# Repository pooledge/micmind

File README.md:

# Micmind - remotely controlled microphone stand prototype (Air P3)
Arduino based microphone stand controlled remotely within a Max/MSP built standalone application. Micmind Air uses a pair of XBee Pro 868 operating in API mode for wireless communication.

This repository includes:
* Arduino sketch to upload on a Pro Mini 328 (5V)
* MaxMSP patch to build a standalone host application for Mac or Windows
* EAGLE files containing schematic and board layouts
* OpenSCAD file enclosure model to build and export in STL format for futher 3D printing
* Xbee firmware XML files used by XCTU
* XML file containing some commands for developing and debuging purposes in XCTU
* Icon file and its .psd source used for the Macintosh standalone

Software versions used at the time building the prototype:
* Mac OS X 10.9.5
* Arduino 1.0.6
* MaxMSP 5.1.3
* EAGLE 7.2.0
* OpenSCAD 2015.03-1
* XCTU 6.2.0
* Photoshop CS6

## What is it about?

Micmind is simply a microphone stand for seamless indoor stereo recording, controlled remotely. So called AB-stereo technique, commonly used in classical music recording utilizes a pair of omnidirectional microphones. While collecting both time-of-arrival and level difference information and being very efficient, this method demands considerations and decisions often being made on-the-fly, also involving some sort of luck. While familiar with theory, sound engineer may still play quite a long time with a stand position and the distance between two microphones as those factors have dramatic impact on the sound image. Very often classical recordings are made with AB only and within low-time conditions, especially those low paid sound engineer jobs if you know what I mean. Now, to tell a long story short, being able to adjust AB parameters from some distance brings following advantages:
* The need to cover multiple meters between control and recording rooms is eliminated (meh)
* Key adjustments applied on-the-fly with their effect to be observed instantly, thus not only the result is achieved in a more efficient way but also the learn effect of using this recording technique increases dramatically.

Micmind is not pretending to be unique, as of 2016 there are different similar products currently available: Remote-Mast, Robo-Mic, Stereoblade, Optogate... etc. However each of them has their disadvantages: summed up they are either too bulky, expensive, loud or not suitable for AB recording due to its size or construction principles.

## Key features
* Up to 1.2km line-of-sight controlling distance
* No frames, rails or cables - end position is freely adjustable
* Linear and rotation movement modes
* Stereo base distance adjustment from 1cm to 99cm
* Impact noise isolation
* Virtual capacitor technology for smoother motion
* Simple and robust modular construction
* Stable grip and low-noise operation

## Safety
* Permanent motor braking while stall
* Panic mode if connection to host computer is lost or not available
* Clear visual status indication both host- and client-side

## Power management
* Single 6c lithium-polymer battery for hours of operation, 5Ah, built-in
* Seamless charging with no disassembly
* Operation/charging mode selector switch

## Chassis
* Main stand built upon freely available Manfrotto 1005BAC tripod and 100mm mecanum wheels
* Simple and efficient 24VDC motors

## Future demands
* ~~Future of Micmind is the future of wireless microphoning. Though our wired initial prototype already serves at it's best, imagine a microphone stand, that can move freely, with no cables, with no boundaries.~~
* ~~Along the embedding of an Xbee modules both host- and client-side for seamless and stable communication, a non-wired future release of Micmind also demands some wireless components to transmit audio signals from floating microphones.~~
* Though a mechanism for height adjustment was initially planned, it was dropped later, as it wasn't possible to retrieve such a non-bulky, low-load, high-stroke component as a serial produced unit. A custom build of a telescopic pipe however may solve this problem, bringing to life an amazing possibility to adjust microphones' position in absolutely all extents without dramatically reducing stand's mobility and stability. 
* Since a homo drive proved to be the right choice for a moveable mic stand, even slightly bigger wheels will instantly allow more stability and better weight distribution - for preciser handling when overcoming boundaries such as cables, height differences of various surfaces and their defects.
* Quieter motors is just a matter of costs, since all their characteristics are already known and have been proved as appropriate. Using gearless motors instead of geared ones might be a good decision, the more so, because the programmable hardware layer of Micmind easily allows their embedding. In that way it is definitely possible to achieve a smoother operation with significant lower noise emission - an important factor for recording classical music known for its wide dynamic range and low SNR.
* ~~PCB, a printed circuit board. This text's author spent two weeks soldering a circuit board for the prototype. Involving more components in the future simply won't leave any choice on this one. For the efficiency of work!~~
* Undo/redo functionality for fast A/B testing

## Disclaimer
This project is being realized as a part of the master degree diploma at the sound engineering faculty of University of music and performing arts in Vienna, Austria.
This disclaimer is being updated constantly along required regulations.

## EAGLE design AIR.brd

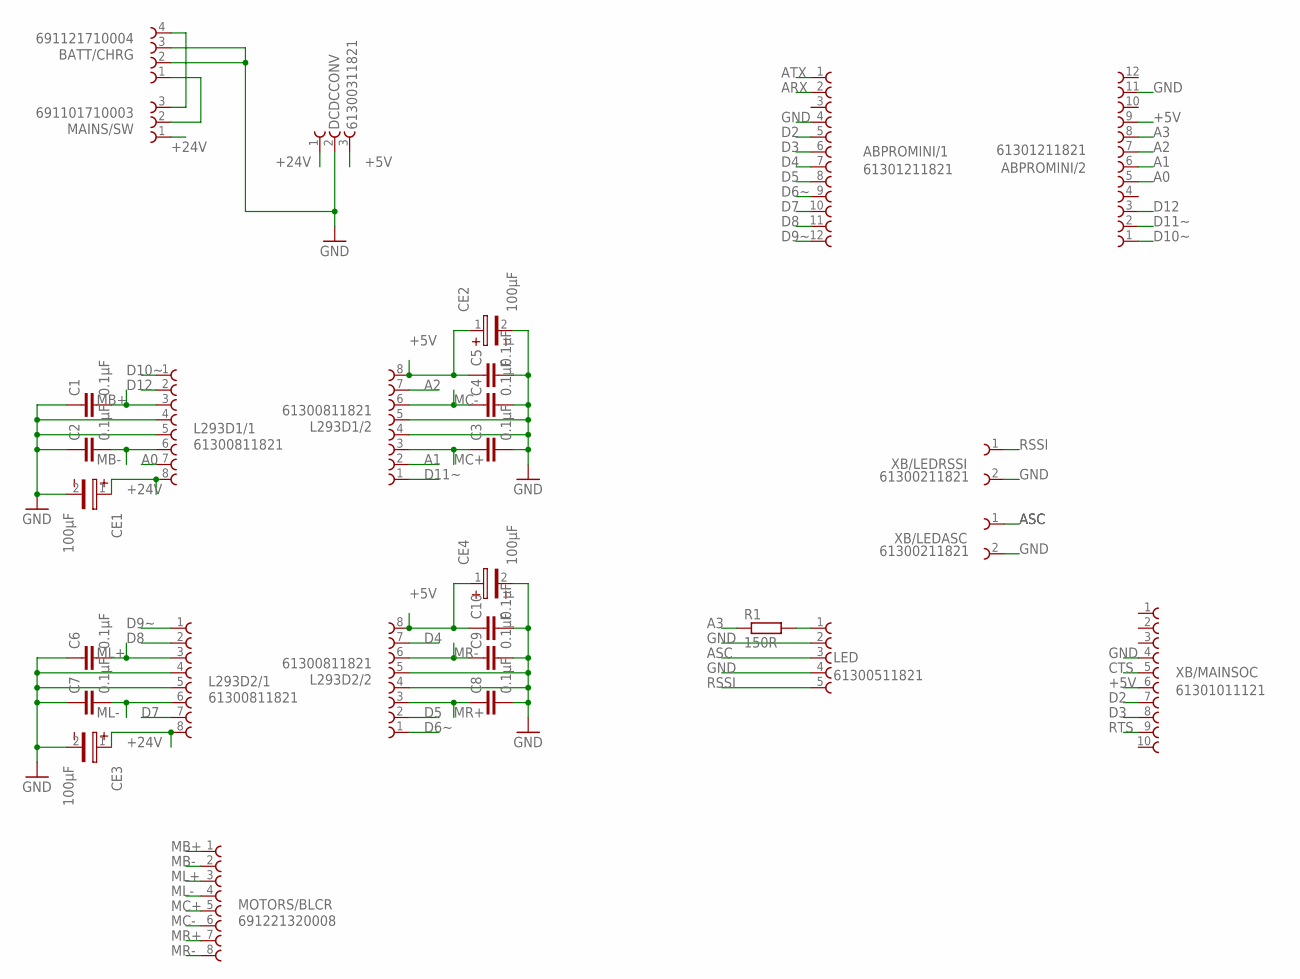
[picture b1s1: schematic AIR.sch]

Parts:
ABPROMINI/1, ABPROMINI/2: 61301211821
BATT/CHRG: 691121710004
C1, C2, C3, C4, C5, C6, C7, C8, C9, C10: 0.1µF; C025-025X050
CE1, CE2, CE3, CE4: 100µF; 8X3.5X0.9(DXAXB)
DCDCCONV: 61300311821
L293D1/1, L293D1/2, L293D2/1, L293D2/2: 61300811821
LED: 61300511821
MAINS/SW: 691101710003
MOTORS/BLCR: 691221320008
R1: 150R; 0204/7
XB/LEDASC: 61300211821
XB/LEDRSSI: 61300211821
XB/MAINSOC: 61301011121

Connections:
+5V: ABPROMINI/2.9, C5.1, C10.1, CE2.1, CE4.1, DCDCCONV.3, L293D1/2.8, L293D2/2.8, XB/MAINSOC.6
+24V: CE1.1, CE3.1, DCDCCONV.1, L293D1/1.8, L293D2/1.8, MAINS/SW.1
A0: ABPROMINI/2.5, L293D1/1.7
A1: ABPROMINI/2.6, L293D1/2.2
A2: ABPROMINI/2.7, L293D1/2.7
A3: ABPROMINI/2.8, R1.1
ARX: ABPROMINI/1.2
ASC: LED.3, XB/LEDASC.1
ATX: ABPROMINI/1.1
CTS: XB/MAINSOC.5
D2: ABPROMINI/1.5, XB/MAINSOC.7
D3: ABPROMINI/1.6, XB/MAINSOC.8
D4: ABPROMINI/1.7, L293D2/2.7
D5: ABPROMINI/1.8, L293D2/2.2
D6~: ABPROMINI/1.9, L293D2/2.1
D7: ABPROMINI/1.10, L293D2/1.7
D8: ABPROMINI/1.11, L293D2/1.2
D9~: ABPROMINI/1.12, L293D2/1.1
D10~: ABPROMINI/2.1, L293D1/1.1
D11~: ABPROMINI/2.2, L293D1/2.1
D12: ABPROMINI/2.3, L293D1/1.2
GND: ABPROMINI/1.4, ABPROMINI/2.11, BATT/CHRG.2, BATT/CHRG.3, C1.1, C2.1, C3.2, C4.2, C5.2, C6.1, C7.1, C8.2, C9.2, C10.2, CE1.2, CE2.2, CE3.2, CE4.2, DCDCCONV.2, L293D1/1.4, L293D1/1.5, L293D1/2.4, L293D1/2.5, L293D2/1.4, L293D2/1.5, L293D2/2.4, L293D2/2.5, LED.2, LED.4, XB/LEDASC.2, XB/LEDRSSI.2, XB/MAINSOC.4
MB+: C1.2, L293D1/1.3, MOTORS/BLCR.1
MB-: C2.2, L293D1/1.6, MOTORS/BLCR.2
MC+: C3.1, L293D1/2.3, MOTORS/BLCR.5
MC-: C4.1, L293D1/2.6, MOTORS/BLCR.6
ML+: C6.2, L293D2/1.3, MOTORS/BLCR.3
ML-: C7.2, L293D2/1.6, MOTORS/BLCR.4
MR+: C8.1, L293D2/2.3, MOTORS/BLCR.7
MR-: C9.1, L293D2/2.6, MOTORS/BLCR.8
unnamed: LED.1, R1.2
unnamed: BATT/CHRG.1, MAINS/SW.2
unnamed: BATT/CHRG.4, MAINS/SW.3
RSSI: LED.5, XB/LEDRSSI.1
RTS: XB/MAINSOC.9

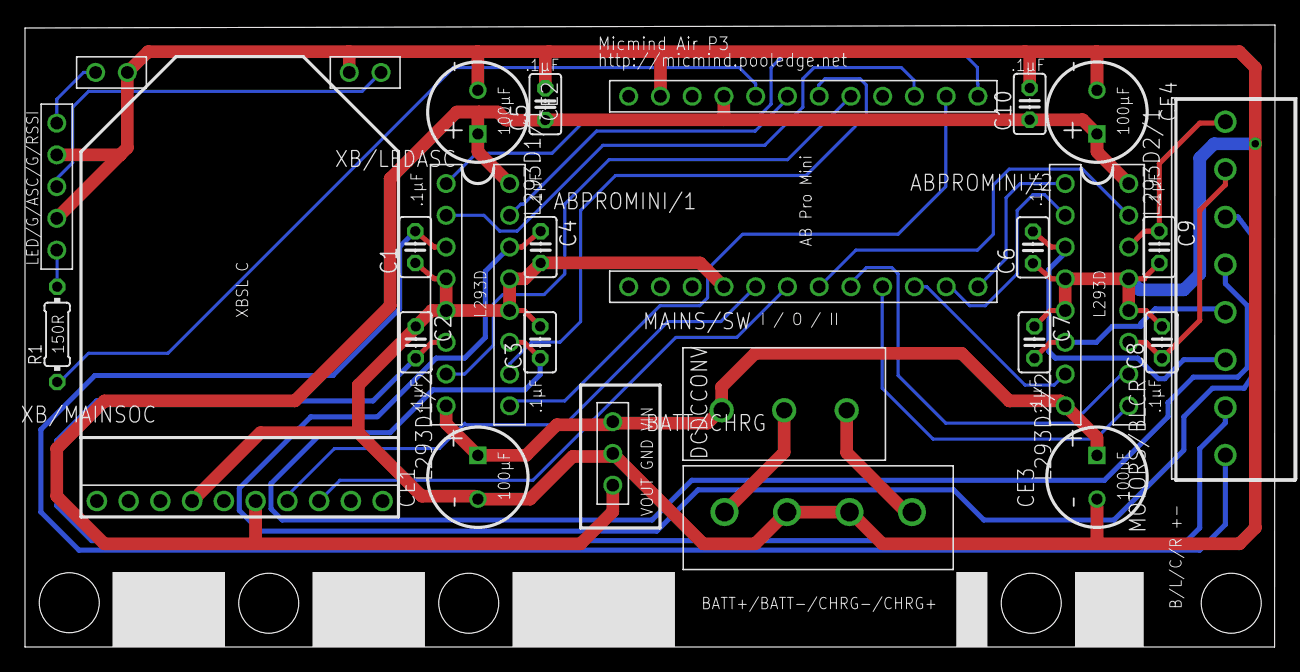
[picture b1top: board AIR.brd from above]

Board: 2 copper layers, 100.0 x 49.8 mm, 29 parts (0 on the bottom side), 31 nets.

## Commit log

2015-05-31 added MaxMSP patch
2015-05-31 Revert fa1ed84..3aadcbb
    This rolls back to commit fa1ed84b8fe8dd335685c7cc3050dde379a0ad21.
2015-05-31 Revert 3aadcbb..7edf3e9
    This rolls back to commit 3aadcbbf141bec8f3076ac76fe7ec85c96751944.
2015-05-31 Revert "Revert 3aadcbb..7edf3e9"
    This reverts commit dd040d5d08a3ce6d9ef825958f68ae29e7dc1ec2.
2015-05-31 Revert 3aadcbb..31a2463
    This rolls back to commit 3aadcbbf141bec8f3076ac76fe7ec85c96751944.
2015-05-31 Added EAGLE Files
2015-06-01 Updated readAPIFrame
2015-06-01 Updated EAGLE files
2015-06-01 Started buildResponse
2015-06-02 buildResponse
2015-06-02 First test run, awaiting flow modifications
2015-06-03 Rudimentary interaction, no reliable status check
2015-06-03 Stability improvements
2015-06-05 First run with XBees fixes and clock improvements
2015-06-06 More polishing on clockery + XCTU frame examples
2015-06-07 Various stability improvements
2015-06-08 First UI, improved stability
2015-06-10 Bugfixes
2015-06-12 Major UI improvements, Arduino and Max files uptd
2015-06-12 New awesome icon and readAPI improvements
2015-06-14 Major stability and UI improvements
    Removed calibration setting from UI, new dynamic AT frame size add-on,
    speed differentiation between roam/base, minor UI tweaka
2015-06-16 Major improvements on hardware, patch stability
2015-06-17 Improved TX power level setting
2015-06-17 PCB updated for integration with LEGO
2015-06-18 Setting TX power level message fix
2015-06-18 Qmetro and hostStatus update
2015-06-22 Minor stabilité fixes
2015-11-02 Added Sketchup file for the enclosure
2015-11-09 SketchUp enclosure model replaced with an OpensCAD
2015-11-21 OpenSCAD update for the enclosure
2015-11-27 OpenSCAD enclosure update
2015-11-27 README updated
2015-11-27 README update
2015-12-13 Updated OpenSCAD enclosure and board
2016-05-02 initial commit, broken apart =(
2016-05-03 still testing, major redesign in readAPI and others, actionUI needs fixing
2016-05-03 quickfix
2016-05-05 stable client connection, todo: coll!, power level
2016-05-05 actionsUI fix
2016-05-05 logging fixed
2016-05-06 fixes
2016-05-08 first stable version of 1.1 - major re-writes, UI-ready, not tested
2016-11-06 undo initial

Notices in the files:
parts and their libraries:
Wurth_Elektronik_Electromechanic_Board_t: Copyright: Würth Elektronik
